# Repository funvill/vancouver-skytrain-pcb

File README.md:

# Vancouver SkyTrain PCB

A printed circuit board that is a map of Metro Vancouver's SkyTrain network,
with one addressable RGB LED per station. Based on
[Idea022 Translink Map PCB](https://blog.abluestar.com/idea022-translink-map-pcb/).

| Version | Where | What |
|---|---|---|
| **v3 (current)** | [`ai-v3/`](ai-v3/) | 200 × 109 mm board, real geography from the BC Freshwater Atlas, station positions from OpenStreetMap, 68 WS2812B LEDs (every current and under-construction station + SeaBus), XIAO controller footprint on the back, generated end-to-end from a data file |
| v2 | [`v2/`](v2/) | 100 × 83 mm schematic-style board, artwork drawn in Inkscape and imported with svg2shenzhen |
| v1 | [`v1/`](v1/) | 320 × 210 mm board with two LEDs per station (one per direction), ESP32 |

**Front** — exposed-copper water, silkscreen routes and station rings, one LED per station:

**Back** — XIAO controller footprint, four buttons, LED chain in/out test points, M3 mounting holes:

Renders are KiCad 10 `kicad-cli pcb render` output (`ai-v3/tools/render_board.py`); the
geography-only preview is `ai-v3/test-results/geo-preview.png`.

## v3 in one paragraph

Everything on the v3 board — LED placement, the exposed-copper water, the
silkscreen routes, station rings and labels, the copper city names and
wordmark — is generated from one data file, `ai-v3/input/vancouver.json`, by
the scripts in `ai-v3/tools/`. The data file is itself built from public
sources (`ai-v3/input/build_from_fwa.py`): the province's Freshwater Atlas
for land, sea, rivers and lakes; OpenStreetMap for station positions; the
province's ABMS layer for the UBC boundary. Labels are laid out by an
optimiser and then finished by hand in KiCad, and the hand edits are pulled
back into the data file so nothing is ever lost to a regeneration.

## Pipeline (v3)

All commands run from `ai-v3/tools/` unless noted. Python 3 with `shapely`,
`numpy`, `scipy`, `pillow`, `matplotlib`; KiCad 10 (its `kicad-cli` is used
for DRC and renders).

### 1. Data

```
cd ai-v3/input
python geo_fwa.py                 # (optional) preview the geography alone -> ../test-results/geo-preview.png
python build_from_fwa.py          # geography + stations + city labels + wordmark -> vancouver.json
cd ../tools
python test_vancouver_data.py     # LED count, chain, pitch, margins
```

`build_from_fwa.py` keeps every station's `label` and the `suppressed_art`
list, so it is safe to re-run after hand edits.

### 2. Labels

```
python auto_label.py                       # greedy placement + simulated annealing
python preview_map.py ../input/vancouver.json ../test-results/preview.png --collisions
python check_fit.py ../input/vancouver.json --scale 2.0 -v
```

`preview_map.py` draws the board exactly as the exporter will (matplotlib,
no KiCad); the red overlay marks collisions.

### 3. Board

```
python export_placement.py ../input/vancouver.json ../hardware --scale 2.0
python reposition_board.py ../hardware/vancouver-skytrain-pcb.kicad_pcb ../hardware/leds.csv --board 200 --height 109
python export_art.py ../input/vancouver.json ../hardware/vancouver-skytrain-pcb.kicad_pcb --scale 2.0
python render_board.py ../hardware/vancouver-skytrain-pcb.kicad_pcb ../test-results
```

`export_art.py` is idempotent: it records every block it writes (uuid → key)
in `vancouver-skytrain-pcb.kicad_pcb.art-manifest.json` and removes them
before writing fresh ones.

### 4. Hand edits in KiCad → back into the data (**import before export**)

Station labels, leader lines and copper text are ordinary `gr_text` /
`gr_line` items. Move, rotate, re-justify, retext or delete them in KiCad,
save, then:

```
python import_labels.py ../input/vancouver.json ../hardware/vancouver-skytrain-pcb.kicad_pcb
```

Each item is found by its deterministic uuid, so the import is exact:

| You did in KiCad | Lands in `vancouver.json` as |
|---|---|
| moved / rotated / re-justified a station label | `label.dx` `dy` `angle` `anchor` (`start` / `end` / `center`) |
| deleted a leader line | leader dropped (`leader` absent) |
| edited a label's text (line break, shorter name) | station `wrap` list, or `label.short` |
| moved a city name or the wordmark | `annotations[i].x` / `y` |
| deleted a piece of generated art (SeaBus dash, route segment, boundary) | key added to `suppressed_art`; the exporter skips it from then on |

**Always run `import_labels.py` before `export_art.py`** — the exporter
regenerates every label from the data file and would otherwise overwrite
the board's hand edits. `import → export` reproduces the board exactly.

## Starting another city

[runbook-new-city.md](runbook-new-city.md) is the step-by-step guide: scope,
station data from OSM, finding authoritative hydrography, the frame and board
size, the data build, labels, hardware, fab and firmware — with the gates to
stop at and a table of what carries over unchanged.

## Lessons learned

See [lessons-learned.md](lessons-learned.md) — what to carry into the next
board of this kind, and the mistakes not to repeat.

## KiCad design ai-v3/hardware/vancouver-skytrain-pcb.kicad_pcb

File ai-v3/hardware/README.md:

# v3 Hardware (KiCad)

Copied from the v2 project, then rewritten by the pipeline:

- **Board outline**: 200 × 109 mm, 5 mm rounded corners, set by
  `reposition_board.py --board 200 --height 109`. The size comes from the
  map frame's aspect (see `../input/geo_fwa.py`), not the other way round.
- **LED1–LED68**: moved to the station positions in `leds.csv` (generated from
  `ai-v3/input/vancouver.json` by `tools/export_placement.py`). LED index =
  ref − 1 = position in the data chain; LED1 is SeaBus, the first in the
  chain. There is no level shifter on v3 — `LED_IN` runs straight from the
  XIAO's pad 8 (D7) into LED1's DI at 3.3 V.
- **U1 (XIAO, back)**: centred on the board; **SW1–SW4** flank it. All DNP.
- **Station labels + land/water art** (F.SilkS text, F.Cu/F.Mask water,
  copper city names and wordmark) generated directly into the board by
  `tools/export_art.py` — no Inkscape/svg2shenzhen step needed. See below.
- The geography in `ai-v3/input/vancouver.json`'s `geo` list is **not**
  hand-drawn: it is built from the BC Freshwater Atlas by
  `../input/geo_fwa.py` and `../input/build_from_fwa.py`. Preview a change
  with `python geo_fwa.py` before regenerating the board.

**Render the board as images** (KiCad's built-in 3D renderer, top-down):

```
python render_board.py ../hardware/vancouver-skytrain-pcb.kicad_pcb ../test-results
```

Writes `board-top.png` and `board-bottom.png`. Pass `--kicad-cli` if
`kicad-cli.exe` isn't at the default `C:\Program Files\KiCad\9.0\bin\`.

Regenerate placements after any layout change:

```
cd ../input && python build_from_fwa.py      # geography + stations + city labels -> vancouver.json
cd ../tools
python export_placement.py ../input/vancouver.json ../hardware --scale 2.0
python reposition_board.py ../hardware/vancouver-skytrain-pcb.kicad_pcb ../hardware/leds.csv --board 200 --height 109
python export_art.py ../input/vancouver.json ../hardware/vancouver-skytrain-pcb.kicad_pcb --scale 2.0
```

The board is **200 × 109 mm** (`board_scale` 2.0 in `vancouver.json`: board mm =
canvas units × 2). Preview the layout without KiCad with
`python preview_map.py ../input/vancouver.json ../test-results/preview.png --collisions`.

**Hand-editing labels in KiCad.** Station labels, their leader lines and the
copper city names / wordmark are ordinary `gr_text` / `gr_line` items — move,
rotate, re-justify, retext or delete them in the PCB editor. Then pull the
edits back into the data file **before** the next `export_art.py` run (which
regenerates every label from `vancouver.json` and would otherwise overwrite
them):

```
python import_labels.py ../input/vancouver.json ../hardware/vancouver-skytrain-pcb.kicad_pcb
```

Each item is found by the deterministic uuid the exporter gave it, so the
import is exact: position/rotation/justification → `label.dx/dy/angle/anchor`,
a deleted leader line → `leader: false`, an edited text → the station's
`wrap` (or `label.short`), a moved city name → `annotations[i].x/y`. A
pre-edit copy of the board and data lives in `backups/` (and git tag
`v3-pre-label-edit`).

Run them in that order (placement first, art second — art positions itself
relative to the current LED footprint locations). `export_art.py` is
idempotent: it tracks every block it writes in
`vancouver-skytrain-pcb.kicad_pcb.art-manifest.json` and removes them before
writing fresh ones, so re-running after an edit to `vancouver.json` never
leaves stale or duplicated art behind.

## Station labels, route lines, and land/water art

`export_art.py` writes native KiCad graphics directly into the `.kicad_pcb`
(not through svg2shenzhen — that path is for hand-drawn art; ours is
generated straight from the same station/geo data as everything else),
styled after TransLink's own "Future Rapid Transit Network" map — one water
colour, filled parks, labelled rivers/municipalities, and a distinct look
for future/under-construction line segments:

- **Route lines** (`route_blocks`) — every line segment from
  `vancouver.json`'s `lines` as an F.SilkS `gr_line`, 1.0 mm wide. A segment
  with either endpoint `future: true` (Broadway Extension, Surrey–Langley
  Extension) is drawn as real **dashed segments** (`dash_points()`) instead
  of one solid line — matching the reference map's "future line" styling.
  Important: KiCad's `(stroke (type dash))` line-*style* property is an
  **editor display hint only** — it does not survive to plotted/fab output
  (SVG export, 3D render, gerbers all flatten it to solid), confirmed by
  testing both here. A genuinely dashed silkscreen line has to be built
  from literal short solid segments with real gaps, which is what
  `dash_points()` does.
- **Station names** — `gr_text` on F.SilkS, same position/rotation math as
  the SVG preview (`citymap.label_box`), 0.15 mm stroke at 1.2 mm. Names
  longer than 13 characters are set on **two lines** (split at the
  official en-dash, else at the middle space — `citymap.display_lines`;
  override per station with `"wrap": [...]` or `"wrap": false`), so the
  abbreviated `short` forms are no longer used on the board. Every label
  anchor sits `LABEL_STANDOFF` (1.9 mm) from the LED centre, clear of the
  pad and ring. A label with `"leader": true` is floated out to its dx/dy
  and joined to the LED by a 0.15 mm hairline — `auto_label.py` uses that
  as a last resort for stations with no clean spot beside the pad, and
  prefers one angle per corridor so the eye tracks a single direction.
- **Station rings** (`station_ring_blocks`) — a silk ring behind every LED
  (r 1.25) so the station reads as circle-on-line; interchanges (`
  "interchange": true`) get a heavier r 1.55 ring. Routes are 1.5 mm.
- **Map furniture** — `geo` entries of `"type": "line"` are plain silk
  polylines with an optional `"dash"` of `dash` / `dot` / `dashdot`
  (SeaBus ferry route, the 49th-parallel border, legend swatches); an
  annotation with `"copper": true` is exposed-copper lettering (F.Cu +
  F.Mask, the gold "VANCOUVER" wordmark from v2).
- **Water** (sea, False Creek, Fraser River) — a filled polygon on **F.Cu**
  with a matching filled polygon on **F.Mask**, so the soldermask opens
  over the copper and it reads as bare copper (gold with ENIG) against the
  black board — the same technique v1 used
  (`v1/input/natrual/natrual/map.kicad_pcb`), generated instead of
  hand-drawn.
- **Land — islands**: thin F.SilkS outline only, no fill (the board
  substrate itself *is* the land, so these just need a boundary).
  **Land — parks**: outline *plus* a 45° diagonal hatch fill
  (`citymap.hatch_fill()`, 1.6 mm spacing) — the single-ink silkscreen
  stand-in for the reference map's solid green park colour. `hatch_fill()`
  is a general scan-line polygon fill (even-odd rule, works on concave
  shapes) so it's reusable for any future city's parks too.
- **Annotations** (`annotation_blocks`) — small F.SilkS text (legend
  labels, CANADA / USA at the border) or copper text (the wordmark). No
  municipality names or water-body labels are printed, by request.

### Station positions and geography: BC Freshwater Atlas + OSM

Water shapes come from the **BC Freshwater Atlas** via
`../input/geo_fwa.py`, and station positions from OpenStreetMap, combined
by `../input/build_from_fwa.py`. The board is **200 × 109 mm**, the aspect
of the lat/lon frame (Point Grey → Langley, North Shore → below Langley)
at 4.33 mm/km; water runs to the board edge (0.4 mm copper-to-edge,
corners pulled inside the 5 mm radius) — there is no border. Earlier
revisions used TransLink's schematic PDF, then v1's hand-drawn map, then
OSM's coastline; see `../input/README.md`. Deliberately not literal:

- Runs whose real spacing is under the LED pitch (downtown, Richmond,
  Sea Island, Coquitlam) are spread outward along their own direction,
  then any remaining too-close pair is separated symmetrically. The
  pitch floor is **3.3 mm**: LED footprints rotate to aim DOUT at the
  next LED, and two diagonal neighbours' pads need that to keep 0.2 mm.
- A station the smoothing leaves inside water (a river-bank station) is
  nudged onto land, as the real map shows it; every LED then gets a
  2.2 mm clearance disk carved out of the copper water.
- The "VANCOUVER" wordmark is exposed-copper lettering placed on land
  (Delta), at the first candidate spot clear of water and track.

Routes are one solid 1.0 mm style for every segment, built or not.
- The Broadway Extension and Surrey–Langley Extension aren't on the
  current-network PDF (not built yet), so those 14 stations are
  extrapolated by continuing each real corridor's traced direction and
  spacing from its last real station.
- Every station's label **direction** (which side of the dot the name
  sits on) is hand-tuned in `vancouver.json`, not traced — the PDF gives
  dot positions, not a reusable label layout. Real station spacing is
  tight enough in a few spots (the airport branch, the Coquitlam bend,
  New Westminster/Columbia/22nd Street) that some labels sit close to a
  neighbour's dot or to the water fill; `check_fit.py` calls these out
  as `label-geo` (expected for coastal stations) vs. real overlaps
  (`label-label`/`label-dot`/`label-line`, hand-fixed one at a time).

### Keeping copper art DRC-clean: `citymap.prepared_geo`

A water/land shape sized for the map doesn't know where the LEDs are, so
raw coordinates from `vancouver.json` will happily overlap LED pads,
bridge the board edge, or trip solder-mask-bridge/clearance rules.
`citymap.prepared_geo(city, scale, avoid_pts)` fixes this once, and
`render_map.py`, `check_fit.py`, and `export_art.py` all call it — so the
SVG preview, the label-collision report, and the physical board always
agree:

1. `densify()` — long polygon edges get intermediate vertices (so a strait
   crossing an LED cluster mid-edge, not just at a vertex, still gets
   caught).
2. `repel()` — any vertex within `keepout` of an LED is pushed away from it.
3. `clamp_to_board()` — vertices are kept inset from the board edge (copper
   needs edge clearance even where the art is meant to visually "bleed" to
   the frame, like the coastline running to the top of the board).
4. `simplify()` (open shapes only, e.g. rivers) — collapses the extra
   densify() vertices back down once they're no longer needed, so a long
   straight run doesn't turn into dozens of tiny render segments.

For **rivers** specifically (drawn as a chain of rectangles, one per
polyline segment, since they have width but no fill), `export_art.py`
adds a final per-segment safety check
(`citymap.poly_point_min_dist`, `RIVER_SAFE_FLOOR`): any rectangle that
still ends up too close to an LED after all of the above is *dropped*
rather than emitted un-safe, and the drop is printed, not silent. On this
board the Fraser River crosses the same tight diagonal corridor the Expo
Line's SkyBridge stations occupy, so several of its segments are
intentionally omitted — the gaps read as the river passing under a
bridge, which is accurate. If you widen station spacing or move the river
line, re-run `export_art.py` and check its printed drop list.

**Known cosmetic-only DRC warnings** (verified non-blocking,
`kicad-cli pcb drc`, 2026-08-30): a handful of `silk_overlap` /
`silk_over_copper` warnings where a station label or a park/island
outline crosses the water fill or another silk element (e.g. Aberdeen's
label crossing the Lulu Island outline). These are `warning`-severity
(KiCad reports them as "Local override" candidates) and are the expected
look of a coastal transit map with exposed-copper water — no station near
the water was going to avoid overlapping it. `clearance` and
`copper_edge_clearance` (the categories that would actually risk a fab
reject or a short) are both **0** after the fixes above.

## Still manual (open in KiCad)

1. **Rotate LEDs for chain routing** — `leds.csv` has the suggested rotation
   (DOUT toward the next chain index); the script deliberately does not touch
   rotation because pad angles must be rewritten by KiCad itself.
2. **Verify U1 orientation**: USB-C must face the bottom board edge (Y+).
3. **Schematic**: v2's sheet is still the source. Confirm the 68-LED chain
   order matches `leds.csv`, add the **74AHC1G125** (C23654) data buffer at
   5 V + 330 Ω series R, decoupling (100 nF per 2 LEDs + 2 × 22 µF bulk), and
   re-annotate/re-sync with the board.
4. Route the data chain and power/ground pours (front + back).
5. DRC, then JLCPCB fab outputs (gerbers / BOM / CPL). Board finish: black
   soldermask, white silk, ENIG (so the exposed-copper water reads gold).

Pre-existing, not caused by the above (present since the v2 copy — schematic
has no routing yet): `unconnected_items`, `shorting_items` (unrouted nets),
`lib_footprint_mismatch` (library version drift), `courtyards_overlap`
(U1/button placement), one `text_height` warning on U1's hidden reference
field, and a `solder_mask_bridge` pair on nearly every LED footprint's own
pads (the XL-1615 library footprint's pads sit close together at that
package size — a library fix, not something the map art caused).

Firmware lives in `../firmware` (PlatformIO, XIAO RP2040, builds clean);
its index tables (`include/firmware_tables.h`) are generated by the same
export — regenerate both together.

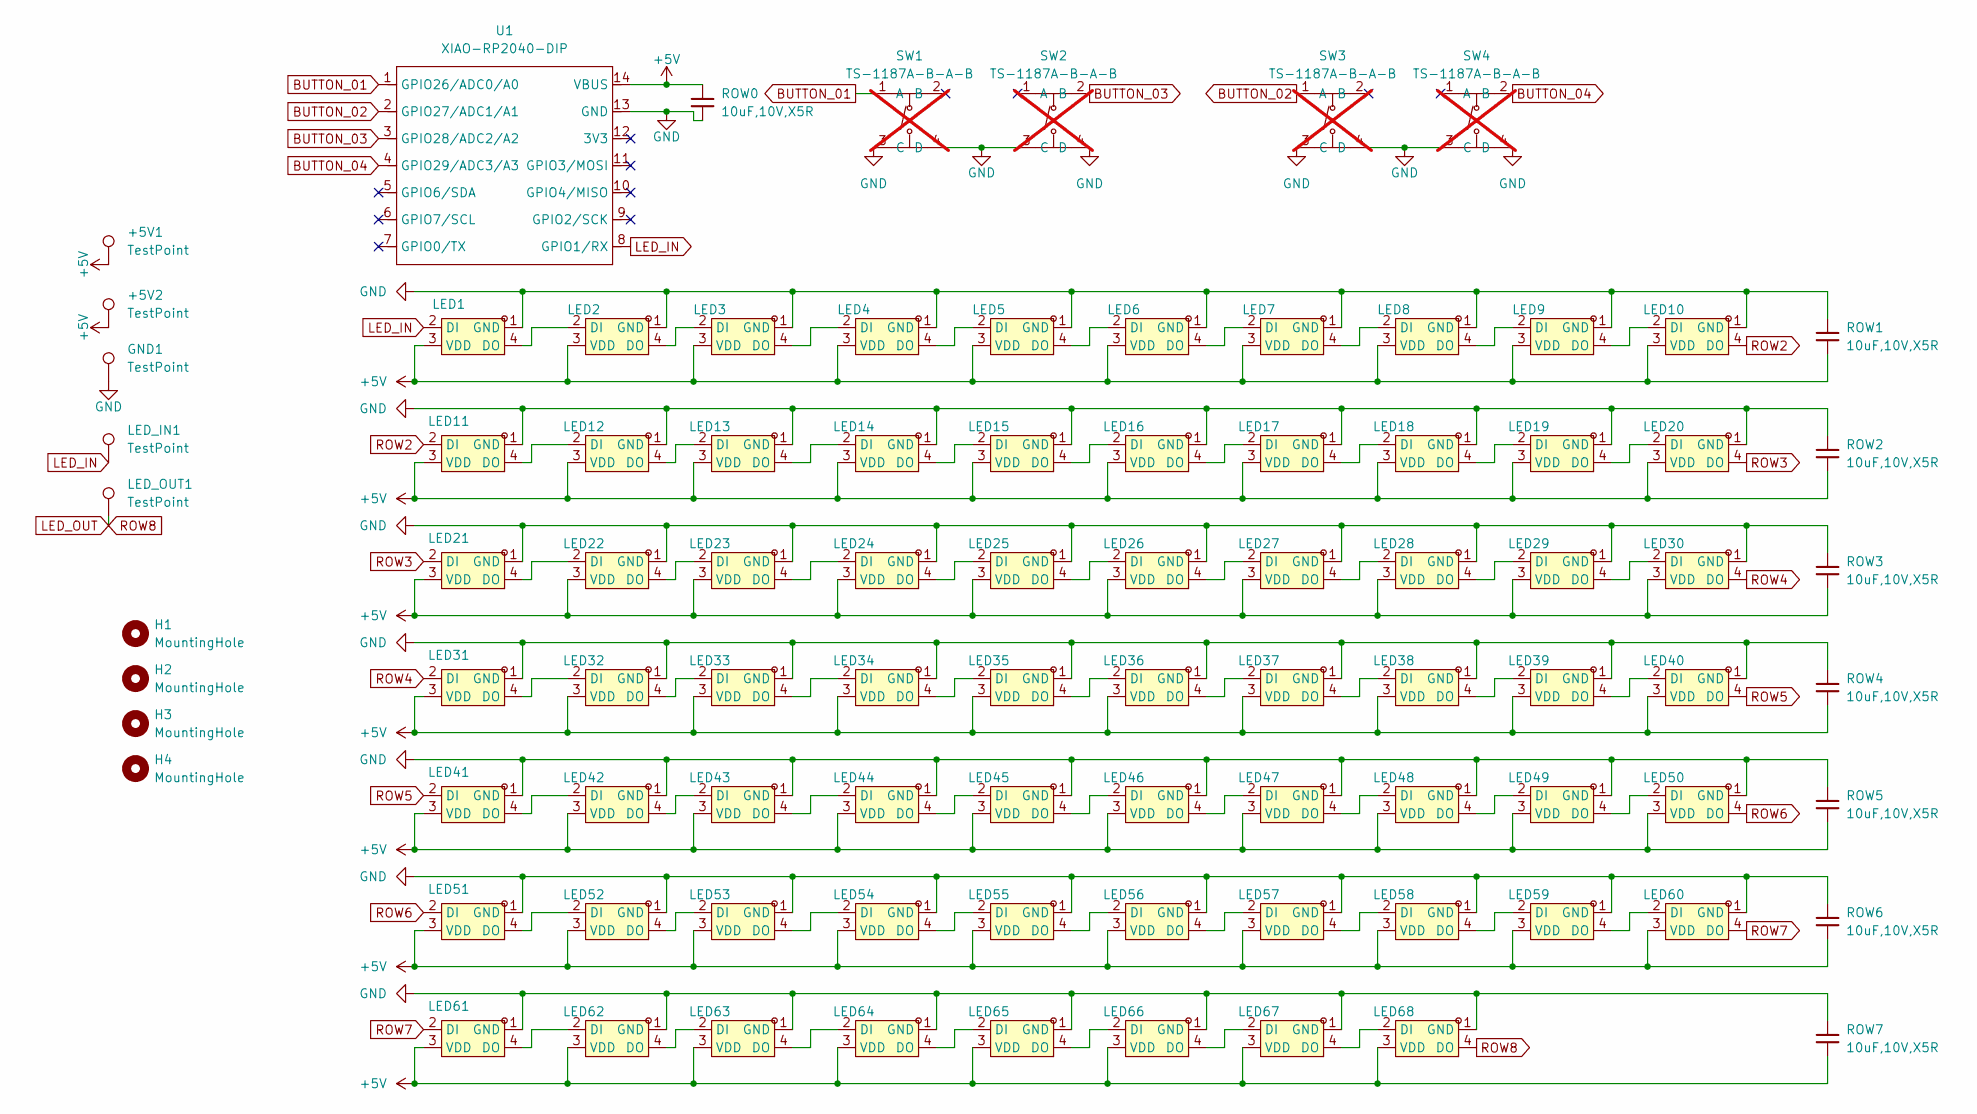
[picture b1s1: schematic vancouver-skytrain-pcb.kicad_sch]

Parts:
+5V1, +5V2: TestPoint; TestPoint_Pad_3.0x3.0mm
GND1: TestPoint; TestPoint_Pad_3.0x3.0mm
H1, H2, H3, H4: MountingHole; MountingHole_3.2mm_M3_DIN965_Pad_TopBottom
LED1, LED2, LED3, LED4, LED5, LED6, LED7, LED8, LED9, LED10, LED11, LED12, LED13, LED14, LED15, LED16, LED17, LED18, LED19, LED20, LED21, LED22, LED23, LED24, LED25, LED26, LED27, LED28, LED29, LED30, LED31, LED32, LED33, LED34, LED35, LED36, LED37, LED38, LED39, LED40, LED41, LED42, LED43, LED44, LED45, LED46, LED47, LED48, LED49, LED50, LED51, LED52, LED53, LED54, LED55, LED56, LED57, LED58, LED59, LED60, LED61, LED62, LED63, LED64, LED65, LED66, LED67, LED68: XL-1615RGBC-WS2812B; LED-SMD_4P-L1.6-W1.5_XL-1615RGBC-WS2812B-1; LCSC Part C5349954
LED_IN1: TestPoint; TestPoint_Pad_3.0x3.0mm
LED_OUT1: TestPoint; TestPoint_Pad_3.0x3.0mm
ROW0, ROW1, ROW2, ROW3, ROW4, ROW5, ROW6, ROW7: 10uF,10V,X5R; C_0402_1005Metric; MFGPN CL05A105KA5NQNC; LCSC C52923
SW1, SW2, SW3, SW4: TS-1187A-B-A-B; SW-SMD_4P-L5.1-W5.1-P3.70-LS6.5-TL_H1.5; LCSC Part C318884; not fitted
U1: XIAO-RP2040-DIP; XIAO-RP2040-SMD

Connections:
+5V: +5V1.1 (1_1), +5V2.1 (1_1), LED1.3 (VDD), LED2.3 (VDD), LED3.3 (VDD), LED4.3 (VDD), LED5.3 (VDD), LED6.3 (VDD), LED7.3 (VDD), LED8.3 (VDD), LED9.3 (VDD), LED10.3 (VDD), LED11.3 (VDD), LED12.3 (VDD), LED13.3 (VDD), LED14.3 (VDD), LED15.3 (VDD), LED16.3 (VDD), LED17.3 (VDD), LED18.3 (VDD), LED19.3 (VDD), LED20.3 (VDD), LED21.3 (VDD), LED22.3 (VDD), LED23.3 (VDD), LED24.3 (VDD), LED25.3 (VDD), LED26.3 (VDD), LED27.3 (VDD), LED28.3 (VDD), LED29.3 (VDD), LED30.3 (VDD), LED31.3 (VDD), LED32.3 (VDD), LED33.3 (VDD), LED34.3 (VDD), LED35.3 (VDD), LED36.3 (VDD), LED37.3 (VDD), LED38.3 (VDD), LED39.3 (VDD), LED40.3 (VDD), LED41.3 (VDD), LED42.3 (VDD), LED43.3 (VDD), LED44.3 (VDD), LED45.3 (VDD), LED46.3 (VDD), LED47.3 (VDD), LED48.3 (VDD), LED49.3 (VDD), LED50.3 (VDD), LED51.3 (VDD), LED52.3 (VDD), LED53.3 (VDD), LED54.3 (VDD), LED55.3 (VDD), LED56.3 (VDD), LED57.3 (VDD), LED58.3 (VDD), LED59.3 (VDD), LED60.3 (VDD), LED61.3 (VDD), LED62.3 (VDD), LED63.3 (VDD), LED64.3 (VDD), LED65.3 (VDD), LED66.3 (VDD), LED67.3 (VDD), LED68.3 (VDD), ROW0.1, ROW1.2, ROW2.2, ROW3.2, ROW4.2, ROW5.2, ROW6.2, ROW7.2, U1.14 (VBUS)
BUTTON_01: SW1.1 (A), U1.1 (GPIO26/ADC0/A0)
BUTTON_02: SW2.1 (A), SW3.1 (A), U1.2 (GPIO27/ADC1/A1)
BUTTON_03: SW2.2 (B), SW3.2 (B), U1.3 (GPIO28/ADC2/A2)
BUTTON_04: SW4.2 (B), U1.4 (GPIO29/ADC3/A3)
GND: GND1.1 (1_1), LED1.1 (GND), LED2.1 (GND), LED3.1 (GND), LED4.1 (GND), LED5.1 (GND), LED6.1 (GND), LED7.1 (GND), LED8.1 (GND), LED9.1 (GND), LED10.1 (GND), LED11.1 (GND), LED12.1 (GND), LED13.1 (GND), LED14.1 (GND), LED15.1 (GND), LED16.1 (GND), LED17.1 (GND), LED18.1 (GND), LED19.1 (GND), LED20.1 (GND), LED21.1 (GND), LED22.1 (GND), LED23.1 (GND), LED24.1 (GND), LED25.1 (GND), LED26.1 (GND), LED27.1 (GND), LED28.1 (GND), LED29.1 (GND), LED30.1 (GND), LED31.1 (GND), LED32.1 (GND), LED33.1 (GND), LED34.1 (GND), LED35.1 (GND), LED36.1 (GND), LED37.1 (GND), LED38.1 (GND), LED39.1 (GND), LED40.1 (GND), LED41.1 (GND), LED42.1 (GND), LED43.1 (GND), LED44.1 (GND), LED45.1 (GND), LED46.1 (GND), LED47.1 (GND), LED48.1 (GND), LED49.1 (GND), LED50.1 (GND), LED51.1 (GND), LED52.1 (GND), LED53.1 (GND), LED54.1 (GND), LED55.1 (GND), LED56.1 (GND), LED57.1 (GND), LED58.1 (GND), LED59.1 (GND), LED60.1 (GND), LED61.1 (GND), LED62.1 (GND), LED63.1 (GND), LED64.1 (GND), LED65.1 (GND), LED66.1 (GND), LED67.1 (GND), LED68.1 (GND), ROW0.2, ROW1.1, ROW2.1, ROW3.1, ROW4.1, ROW5.1, ROW6.1, ROW7.1, SW1.3 (C), SW1.4 (D), SW2.3 (C), SW2.4 (D), SW3.3 (C), SW3.4 (D), SW4.3 (C), SW4.4 (D), U1.13 (GND)
LED_IN: LED1.2 (DI), LED_IN1.1 (1_1), U1.8 (GPIO1/RX)
LED_OUT: LED68.4 (DO), LED_OUT1.1 (1_1)
unnamed: LED1.4 (DO), LED2.2 (DI)
unnamed: LED2.4 (DO), LED3.2 (DI)
unnamed: LED3.4 (DO), LED4.2 (DI)
unnamed: LED4.4 (DO), LED5.2 (DI)
unnamed: LED5.4 (DO), LED6.2 (DI)
unnamed: LED6.4 (DO), LED7.2 (DI)
unnamed: LED7.4 (DO), LED8.2 (DI)
unnamed: LED8.4 (DO), LED9.2 (DI)
unnamed: LED9.4 (DO), LED10.2 (DI)
unnamed: LED11.4 (DO), LED12.2 (DI)
unnamed: LED12.4 (DO), LED13.2 (DI)
unnamed: LED13.4 (DO), LED14.2 (DI)
unnamed: LED14.4 (DO), LED15.2 (DI)
unnamed: LED15.4 (DO), LED16.2 (DI)
unnamed: LED16.4 (DO), LED17.2 (DI)
unnamed: LED17.4 (DO), LED18.2 (DI)
unnamed: LED18.4 (DO), LED19.2 (DI)
unnamed: LED19.4 (DO), LED20.2 (DI)
unnamed: LED21.4 (DO), LED22.2 (DI)
unnamed: LED22.4 (DO), LED23.2 (DI)
unnamed: LED23.4 (DO), LED24.2 (DI)
unnamed: LED24.4 (DO), LED25.2 (DI)
unnamed: LED25.4 (DO), LED26.2 (DI)
unnamed: LED26.4 (DO), LED27.2 (DI)
unnamed: LED27.4 (DO), LED28.2 (DI)
unnamed: LED28.4 (DO), LED29.2 (DI)
unnamed: LED29.4 (DO), LED30.2 (DI)
unnamed: LED31.4 (DO), LED32.2 (DI)
unnamed: LED32.4 (DO), LED33.2 (DI)
unnamed: LED33.4 (DO), LED34.2 (DI)
unnamed: LED34.4 (DO), LED35.2 (DI)
unnamed: LED35.4 (DO), LED36.2 (DI)
unnamed: LED36.4 (DO), LED37.2 (DI)
unnamed: LED37.4 (DO), LED38.2 (DI)
unnamed: LED38.4 (DO), LED39.2 (DI)
unnamed: LED39.4 (DO), LED40.2 (DI)
unnamed: LED41.4 (DO), LED42.2 (DI)
unnamed: LED42.4 (DO), LED43.2 (DI)
unnamed: LED43.4 (DO), LED44.2 (DI)
unnamed: LED44.4 (DO), LED45.2 (DI)
unnamed: LED45.4 (DO), LED46.2 (DI)
unnamed: LED46.4 (DO), LED47.2 (DI)
unnamed: LED47.4 (DO), LED48.2 (DI)
unnamed: LED48.4 (DO), LED49.2 (DI)
unnamed: LED49.4 (DO), LED50.2 (DI)
unnamed: LED51.4 (DO), LED52.2 (DI)
unnamed: LED52.4 (DO), LED53.2 (DI)
unnamed: LED53.4 (DO), LED54.2 (DI)
unnamed: LED54.4 (DO), LED55.2 (DI)
unnamed: LED55.4 (DO), LED56.2 (DI)
unnamed: LED56.4 (DO), LED57.2 (DI)
unnamed: LED57.4 (DO), LED58.2 (DI)
unnamed: LED58.4 (DO), LED59.2 (DI)
unnamed: LED59.4 (DO), LED60.2 (DI)
unnamed: LED61.4 (DO), LED62.2 (DI)
unnamed: LED62.4 (DO), LED63.2 (DI)
unnamed: LED63.4 (DO), LED64.2 (DI)
unnamed: LED64.4 (DO), LED65.2 (DI)
unnamed: LED65.4 (DO), LED66.2 (DI)
unnamed: LED66.4 (DO), LED67.2 (DI)
unnamed: LED67.4 (DO), LED68.2 (DI)
ROW2: LED10.4 (DO), LED11.2 (DI)
ROW3: LED20.4 (DO), LED21.2 (DI)
ROW4: LED30.4 (DO), LED31.2 (DI)
ROW5: LED40.4 (DO), LED41.2 (DI)
ROW6: LED50.4 (DO), LED51.2 (DI)
ROW7: LED60.4 (DO), LED61.2 (DI)

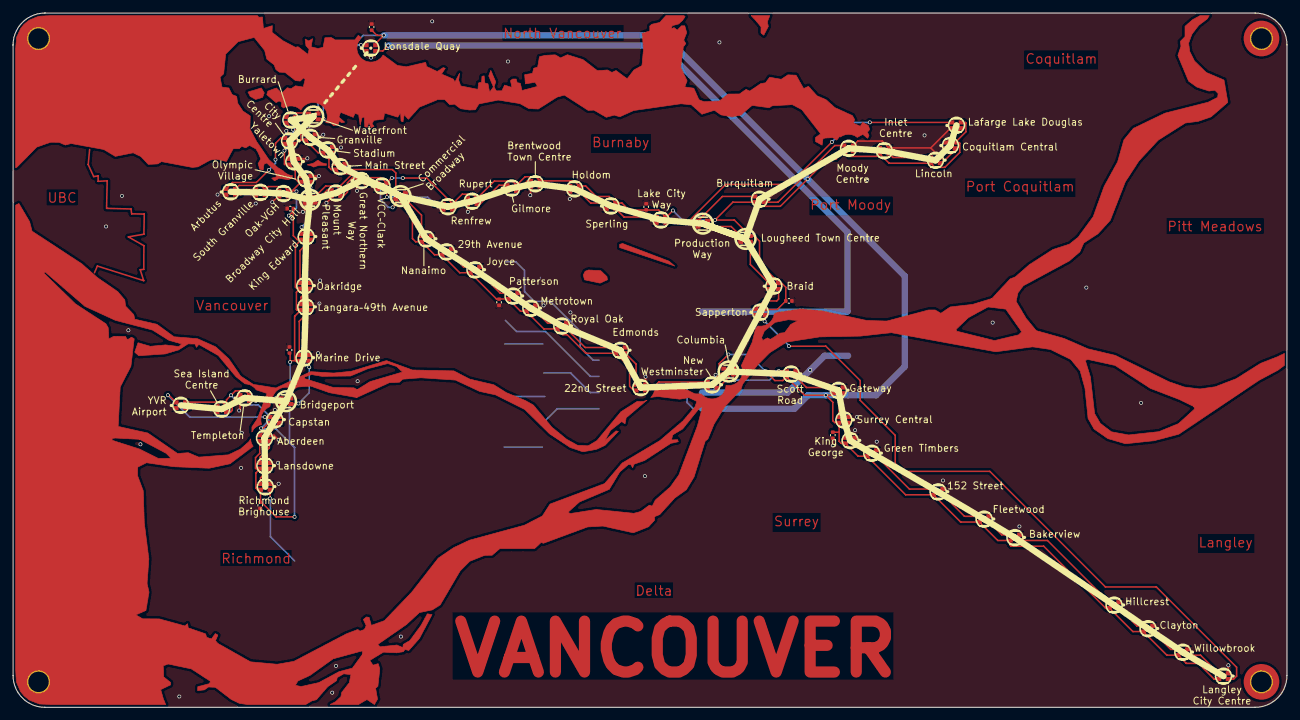
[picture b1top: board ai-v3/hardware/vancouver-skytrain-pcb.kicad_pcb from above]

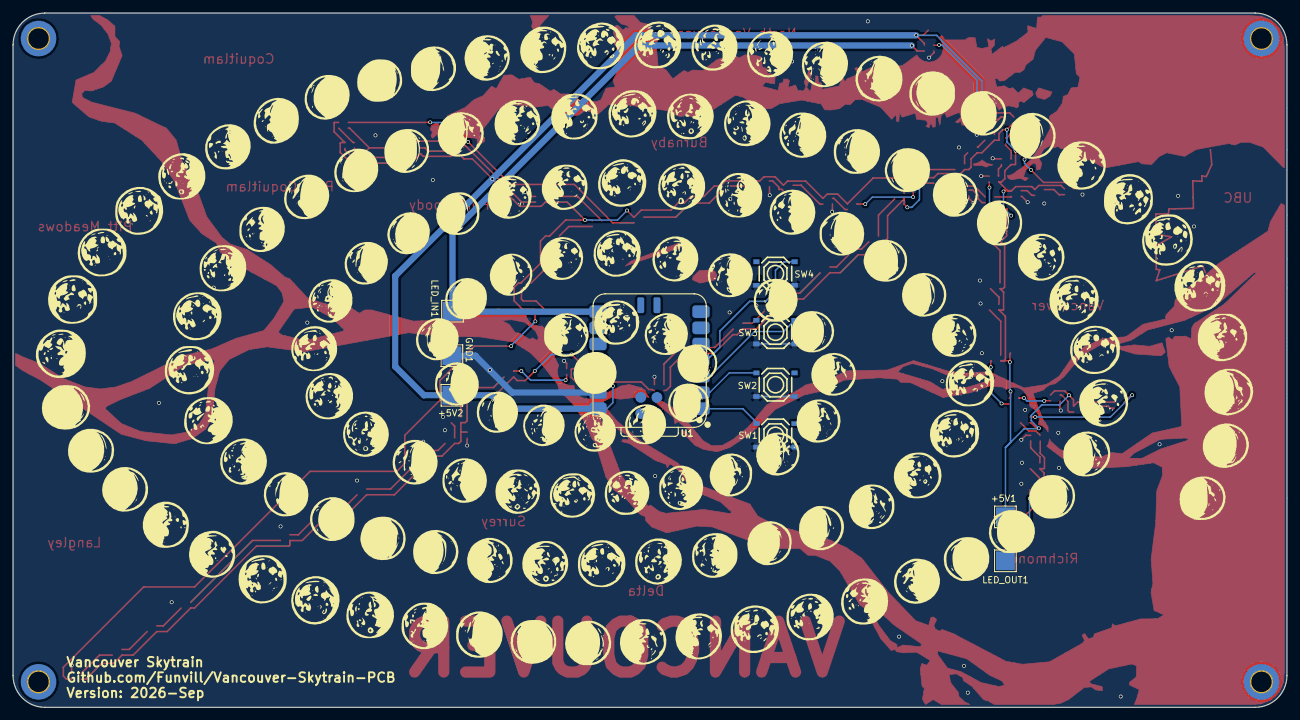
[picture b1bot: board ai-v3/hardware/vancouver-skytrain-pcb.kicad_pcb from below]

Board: 2 copper layers, 200.0 x 109.0 mm, 90 parts (10 on the bottom side), 75 nets.

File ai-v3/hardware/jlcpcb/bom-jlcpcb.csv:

Comment,Designator,Footprint,LCSC Part #
XL-1615RGBC-WS2812B,"LED1,LED2,LED3,LED4,LED5,LED6,LED7,LED8,LED9,LED10,LED11,LED12,LED13,LED14,LED15,LED16,LED17,LED18,LED19,LED20,LED21,LED22,LED23,LED24,LED25,LED26,LED27,LED28,LED29,LED30,LED31,LED32,LED33,LED34,LED35,LED36,LED37,LED38,LED39,LED40,LED41,LED42,LED43,LED44,LED45,LED46,LED47,LED48,LED49,LED50,LED51,LED52,LED53,LED54,LED55,LED56,LED57,LED58,LED59,LED60,LED61,LED62,LED63,LED64,LED65,LED66,LED67,LED68",LED-SMD_4P-L1.6-W1.5_XL-1615RGBC-WS2812B-1,C5349954
"10uF,10V,X5R","ROW0,ROW1,ROW2,ROW3,ROW4,ROW5,ROW6,ROW7",C_0402_1005Metric,C52923
